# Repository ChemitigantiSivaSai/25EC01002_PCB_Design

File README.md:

# 25EC01002_PCB_Design

EC2L104 – Introduction to EDA Tools (IIT Bhubaneswar), Module 10 laboratory work  
**Chemitiganti Siva Sai – 25EC01002**

A discrete CMOS inverter (2N7000 NMOS + BS250 PMOS, 5 V, LED output indicator) taken from
LTspice simulation to a two-layer KiCad 10 PCB with fabrication files.

## Repository layout
| Folder | Content |
|---|---|
| `ltspice/` | LTspice schematics (.asc), manufacturer model libraries (2N7000 onsemi, BS250 Philips), logs, exported VTC data (5 V and 9 V), 65 nm VTC export, `ex5_opt1/` (buffer schematics `Buffer_DC.asc` and `Buffer_TRAN.asc`, netlists, logs, exports, raw) and `ex5_opt2/` runs |
| `python/` | `plot_vtc_discrete.py` (L4 - VTC with VM marked, 300 dpi PNG), `plot_overlay_65nm.py` (L5 - normalised overlay), `plot_vtc_compare_ex5.py` (option 2 VTC overlay), `plot_buffer_ex5_opt1.py` (option 1 buffer VTC and delay) |
| `kicad/25EC01002_INV/` | Exercise 1-4 KiCad project (`.kicad_pro/.kicad_sch/.kicad_pcb`), BOM CSV, ERC/DRC reports, `gerbers/` (Gerbers + drill files) |
| `kicad/ex5_opt1/`, `ex5_opt2/`, `ex5_opt3/`, `ex5_opt4/` | Exercise 5 projects, one per option, each with its own Gerbers |
| `docs/` | Lab report (PDF), its LaTeX source in `docs/latex/`, and screenshots |

## Key results (Exercises 0-4)
- Switching threshold VM = 2.349 V (VDD = 5 V, manufacturer SPICE models); VOH = 4.94 V, VOL ~ 0 V; VM = 4.07 V at VDD = 9 V
- LED current 4.25 mA with R1 = 1 kohm (simulated, 2N7000 onsemi + BS250 Philips models)
- Board: 50 x 40 mm, 2-layer, 4 x M3 holes, ground pour on B.Cu
- ERC: 0 errors / 0 warnings; DRC: 0 violations, 0 unconnected, 0 parity errors

## Exercise 5 (extra explorations)
Each option was done on its own copy of the Exercise 4 project.

| Option | Where | Result |
|---|---|---|
| 1 - second inverter stage (non-inverting buffer) | `kicad/ex5_opt1/`, `ltspice/ex5_opt1/`, `python/plot_buffer_ex5_opt1.py` | VM 2.415 V (both stages), tpLH 16.4 ns / tpHL 16.8 ns, LED lit when VIN high; board still 50 x 40 mm, R1/D1 moved 7.5 mm, copper 214.5 -> 253.9 mm, DRC 0/0/0 |
| 2 - LED lights when output is low | `kicad/ex5_opt2/`, `ltspice/ex5_opt2/`, `python/plot_vtc_compare_ex5.py` | VM 2.35 V -> 2.48 V, LED current 4.29 mA now through the NMOS, +17.5 mm copper, DRC 0/0/0 |
| 3 - minimum clearance 0.4 mm | `kicad/ex5_opt3/` | Q1/Q2 changed to `TO-92_Inline_Wide` (pad gap 0.22 -> 1.04 mm), board unchanged, DRC 0/0/0 |
| 4 - trimpot replaced by 2-pin header J3, board shrunk | `kicad/ex5_opt4/` | Board 50 x 40 -> 34 x 29 mm, copper 214.5 -> 82.4 mm, DRC 0/0/0 |

## Run the plots
```
cd python
python plot_vtc_discrete.py "../ltspice/circuit VDD =5V.txt"   # -> CMOS_Inverter_VTC.png
python plot_overlay_65nm.py                                    # -> VTC_overlay_normalised.png
python plot_buffer_ex5_opt1.py ../ltspice/ex5_opt1/buffer_DC.txt ../ltspice/ex5_opt1/buffer_TRAN.raw   # -> buffer_ex5_opt1.png
```
Requires Python 3 with numpy, pandas, matplotlib.

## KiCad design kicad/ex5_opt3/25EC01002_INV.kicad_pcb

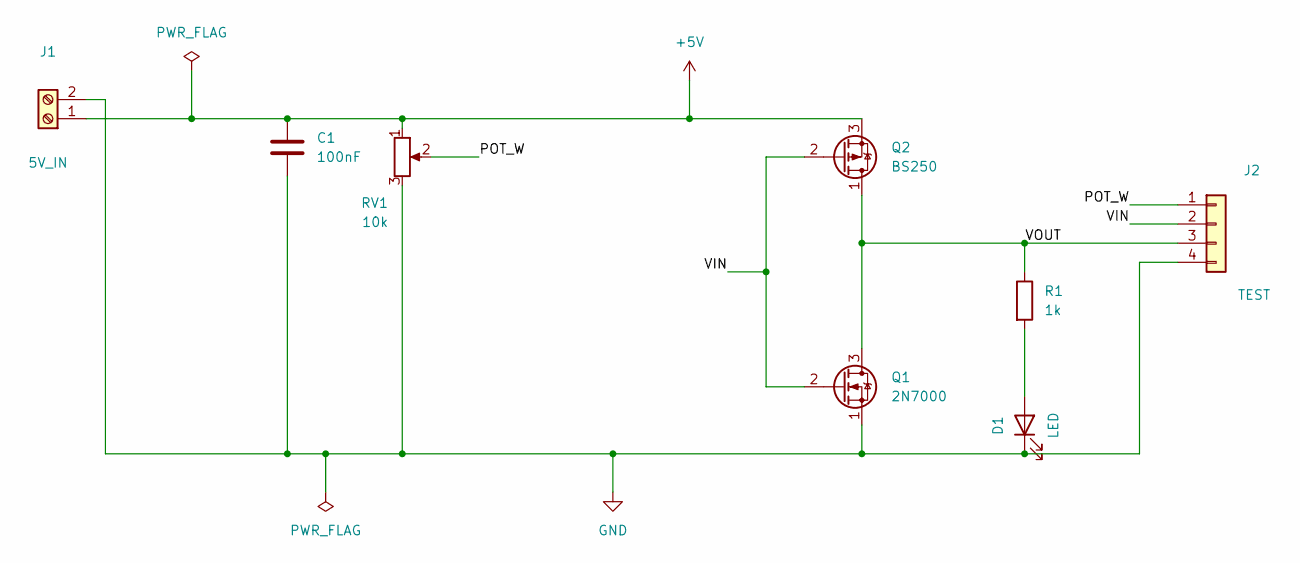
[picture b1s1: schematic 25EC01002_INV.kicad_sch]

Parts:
C1: 100nF; C_Disc_D5.0mm_W2.5mm_P5.00mm
D1: LED; LED_D3.0mm
J1: 5V_IN; TerminalBlock_Phoenix_MKDS-1,5-2-5.08_1x02_P5.08mm_Horizont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
J2: TEST; PinHeader_1x04_P2.54mm_Vertical
Q1: 2N7000; TO-92_Inline_Wide
Q2: BS250; TO-92_Inline_Wide
R1: 1k; R_Axial_DIN0207_L6.3mm_D2.5mm_P10.16mm_Horizontal
RV1: 10k; Potentiometer_Bourns_3386P_Vertical

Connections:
+5V: C1.1, J1.1, Q2.3 (S), RV1.1
/POT_W: J2.1, RV1.2
/VIN: J2.2, Q1.2 (G), Q2.2 (G)
/VOUT: J2.3, Q1.3 (D), Q2.1 (D), R1.1
GND: C1.2, D1.1 (K), J1.2, J2.4, Q1.1 (S), RV1.3
unnamed: D1.2 (A), R1.2

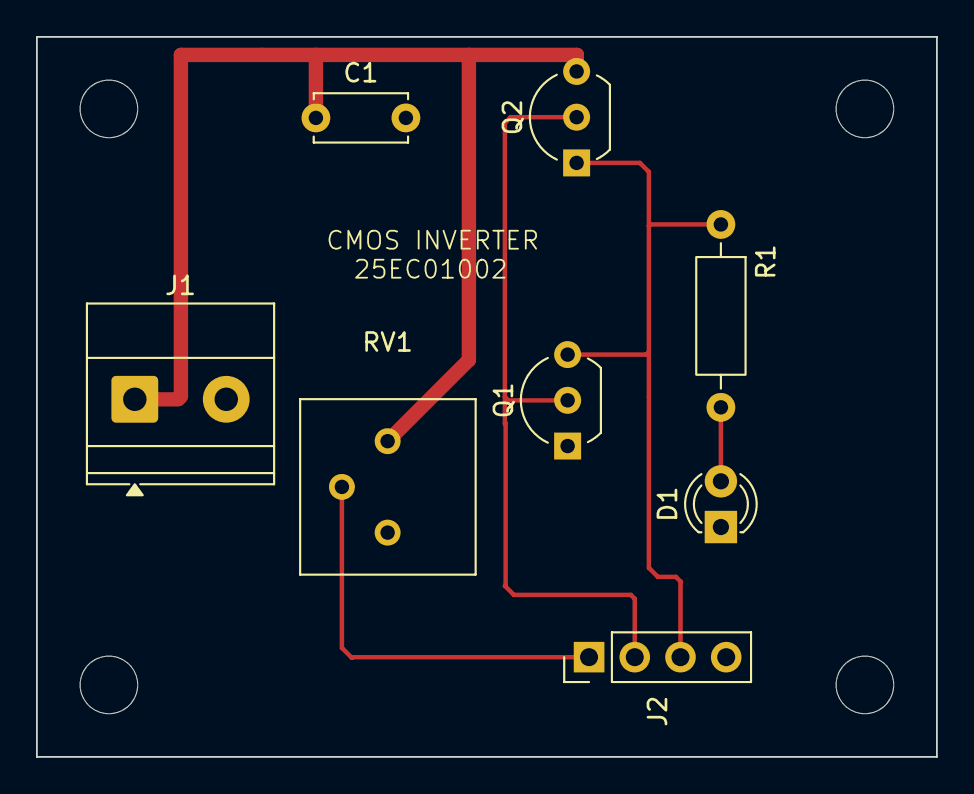
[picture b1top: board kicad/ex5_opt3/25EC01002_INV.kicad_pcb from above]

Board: 2 copper layers, 50.0 x 40.0 mm, 8 parts (0 on the bottom side), 6 nets.

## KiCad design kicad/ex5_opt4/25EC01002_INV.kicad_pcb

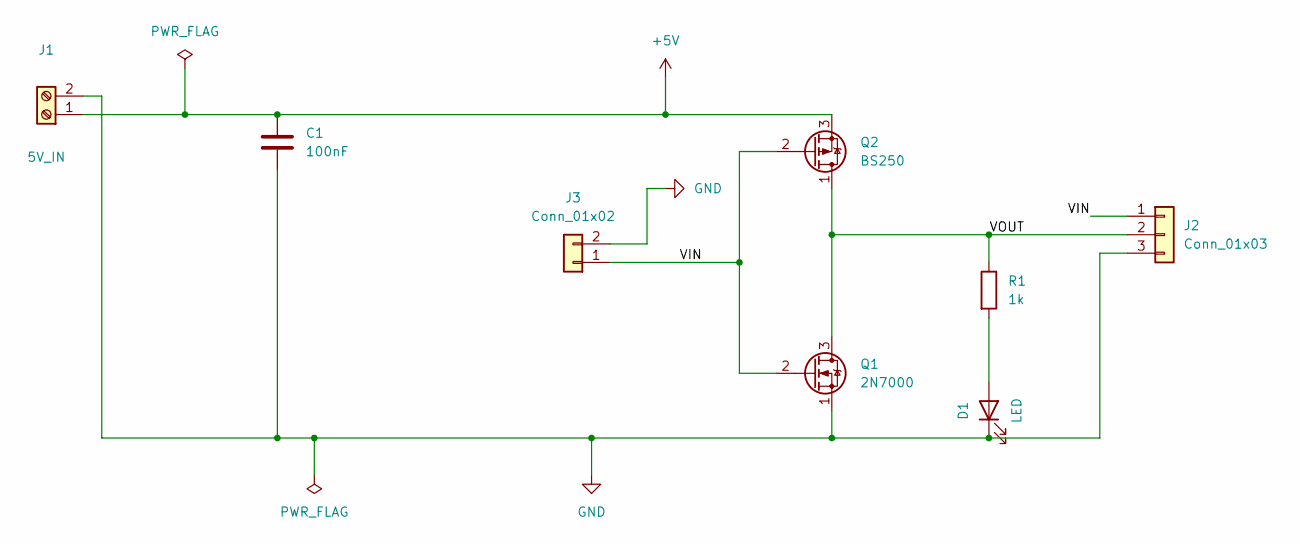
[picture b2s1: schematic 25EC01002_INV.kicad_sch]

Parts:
C1: 100nF; C_Disc_D5.0mm_W2.5mm_P5.00mm
D1: LED; LED_D3.0mm
J1: 5V_IN; TerminalBlock_Phoenix_MKDS-1,5-2-5.08_1x02_P5.08mm_Horizont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
J2: Conn_01x03; PinHeader_1x03_P2.54mm_Vertical
J3: Conn_01x02; PinHeader_1x02_P2.54mm_Vertical
Q1: 2N7000; TO-92_Inline
Q2: BS250; TO-92_Inline
R1: 1k; R_Axial_DIN0207_L6.3mm_D2.5mm_P10.16mm_Horizontal

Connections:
+5V: C1.1, J1.1, Q2.3 (S)
/VIN: J2.1, J3.1, Q1.2 (G), Q2.2 (G)
/VOUT: J2.2, Q1.3 (D), Q2.1 (D), R1.1
GND: C1.2, D1.1 (K), J1.2, J2.3, J3.2, Q1.1 (S)
unnamed: D1.2 (A), R1.2

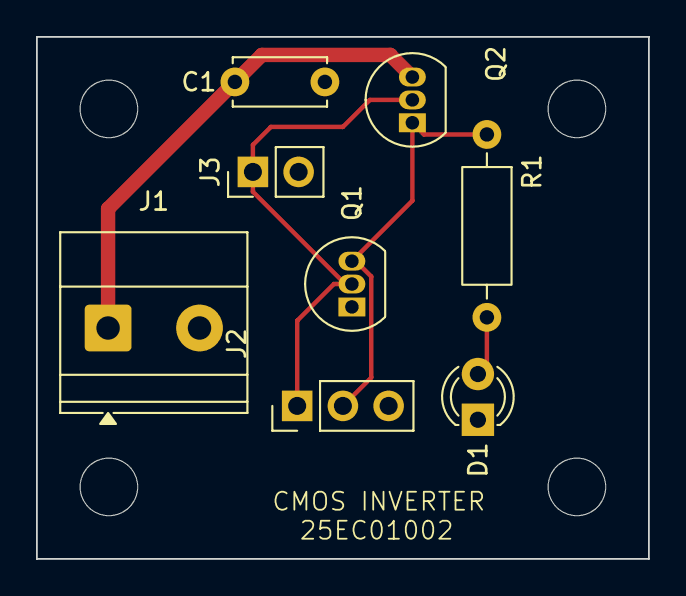
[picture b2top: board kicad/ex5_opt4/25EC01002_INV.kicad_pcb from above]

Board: 2 copper layers, 34.0 x 29.0 mm, 8 parts (0 on the bottom side), 5 nets.
